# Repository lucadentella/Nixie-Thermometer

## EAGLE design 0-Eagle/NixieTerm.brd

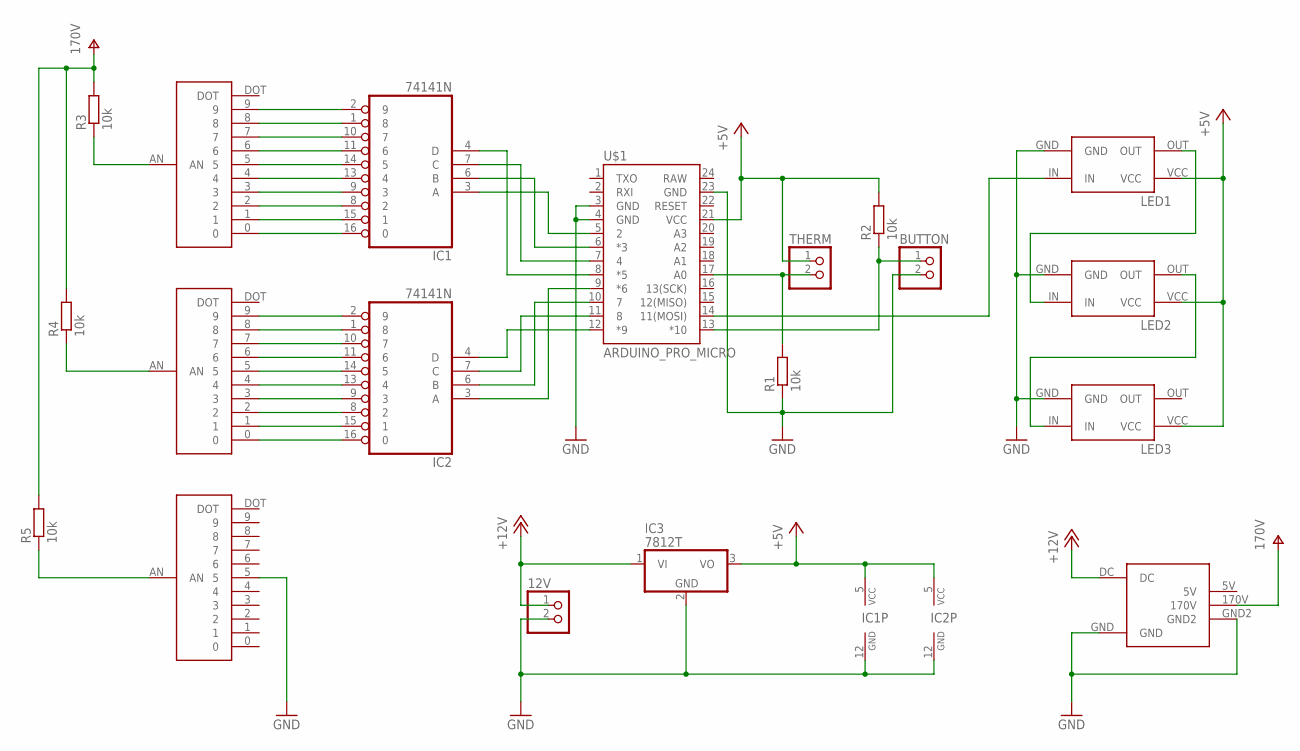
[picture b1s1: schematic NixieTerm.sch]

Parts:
12V: PINHD-1X2; 1X02
BUTTON: PINHD-1X2; 1X02
DEC: NIXIE-SOCKET; NIXIE-SOCKET-PAC
IC1, IC2: 74141N; DIL16
IC3: 7812T; TO220H
LED1, LED2, LED3: WS2812-LED; WS2812-LED-PAC
R1, R2, R3, R4, R5: 10k; 0207/12
SYM: NIXIE-SOCKET; NIXIE-SOCKET-PAC
THERM: PINHD-1X2; 1X02
U$1: ARDUINO_PRO_MICRO
U$2: NIXIE-SUPPLY; NIXIE-SUPPLY-PAC
UNIT: NIXIE-SOCKET; NIXIE-SOCKET-PAC

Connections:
+5V: IC1.5 (VCC), IC2.5 (VCC), IC3.3 (VO), LED1.VCC, LED2.VCC, LED3.VCC, R2.2, THERM.1, U$1.21 (VCC)
+12V: 12V.1, IC3.1 (VI), U$2.DC
GND: 12V.2, BUTTON.2, IC1.12 (GND), IC2.12 (GND), IC3.2 (GND), LED1.GND, LED2.GND, LED3.GND, R1.1, SYM.5, U$1.3 (GND), U$1.4 (GND), U$1.23 (GND), U$2.GND, U$2.GND2
unnamed: IC1.3 (A), U$1.5 (2)
unnamed: IC1.6 (B), U$1.6 (*3)
unnamed: IC1.7 (C), U$1.7 (4)
unnamed: IC1.4 (D), U$1.8 (*5)
unnamed: IC2.3 (A), U$1.9 (*6)
unnamed: IC2.6 (B), U$1.10 (7)
unnamed: IC2.7 (C), U$1.11 (8)
unnamed: IC2.4 (D), U$1.12 (*9)
unnamed: R1.2, THERM.2, U$1.17 (A0)
unnamed: BUTTON.1, R2.1, U$1.13 (*10)
unnamed: DEC.9, IC1.2 (9)
unnamed: LED1.OUT, LED2.IN
unnamed: LED2.OUT, LED3.IN
unnamed: LED1.IN, U$1.14 (11(MOSI))
unnamed: DEC.8, IC1.1 (8)
unnamed: DEC.7, IC1.10 (7)
unnamed: DEC.6, IC1.11 (6)
unnamed: DEC.5, IC1.14 (5)
unnamed: DEC.4, IC1.13 (4)
unnamed: DEC.3, IC1.9 (3)
unnamed: DEC.2, IC1.8 (2)
unnamed: DEC.1, IC1.15 (1)
unnamed: DEC.0, IC1.16 (0)
unnamed: IC2.2 (9), UNIT.9
unnamed: IC2.1 (8), UNIT.8
unnamed: IC2.10 (7), UNIT.7
unnamed: IC2.11 (6), UNIT.6
unnamed: IC2.14 (5), UNIT.5
unnamed: IC2.13 (4), UNIT.4
unnamed: IC2.9 (3), UNIT.3
unnamed: IC2.8 (2), UNIT.2
unnamed: IC2.15 (1), UNIT.1
unnamed: IC2.16 (0), UNIT.0
unnamed: DEC.AN, R3.1
unnamed: R4.1, UNIT.AN
unnamed: R5.1, SYM.AN
V+: R3.2, R4.2, R5.2, U$2.170V

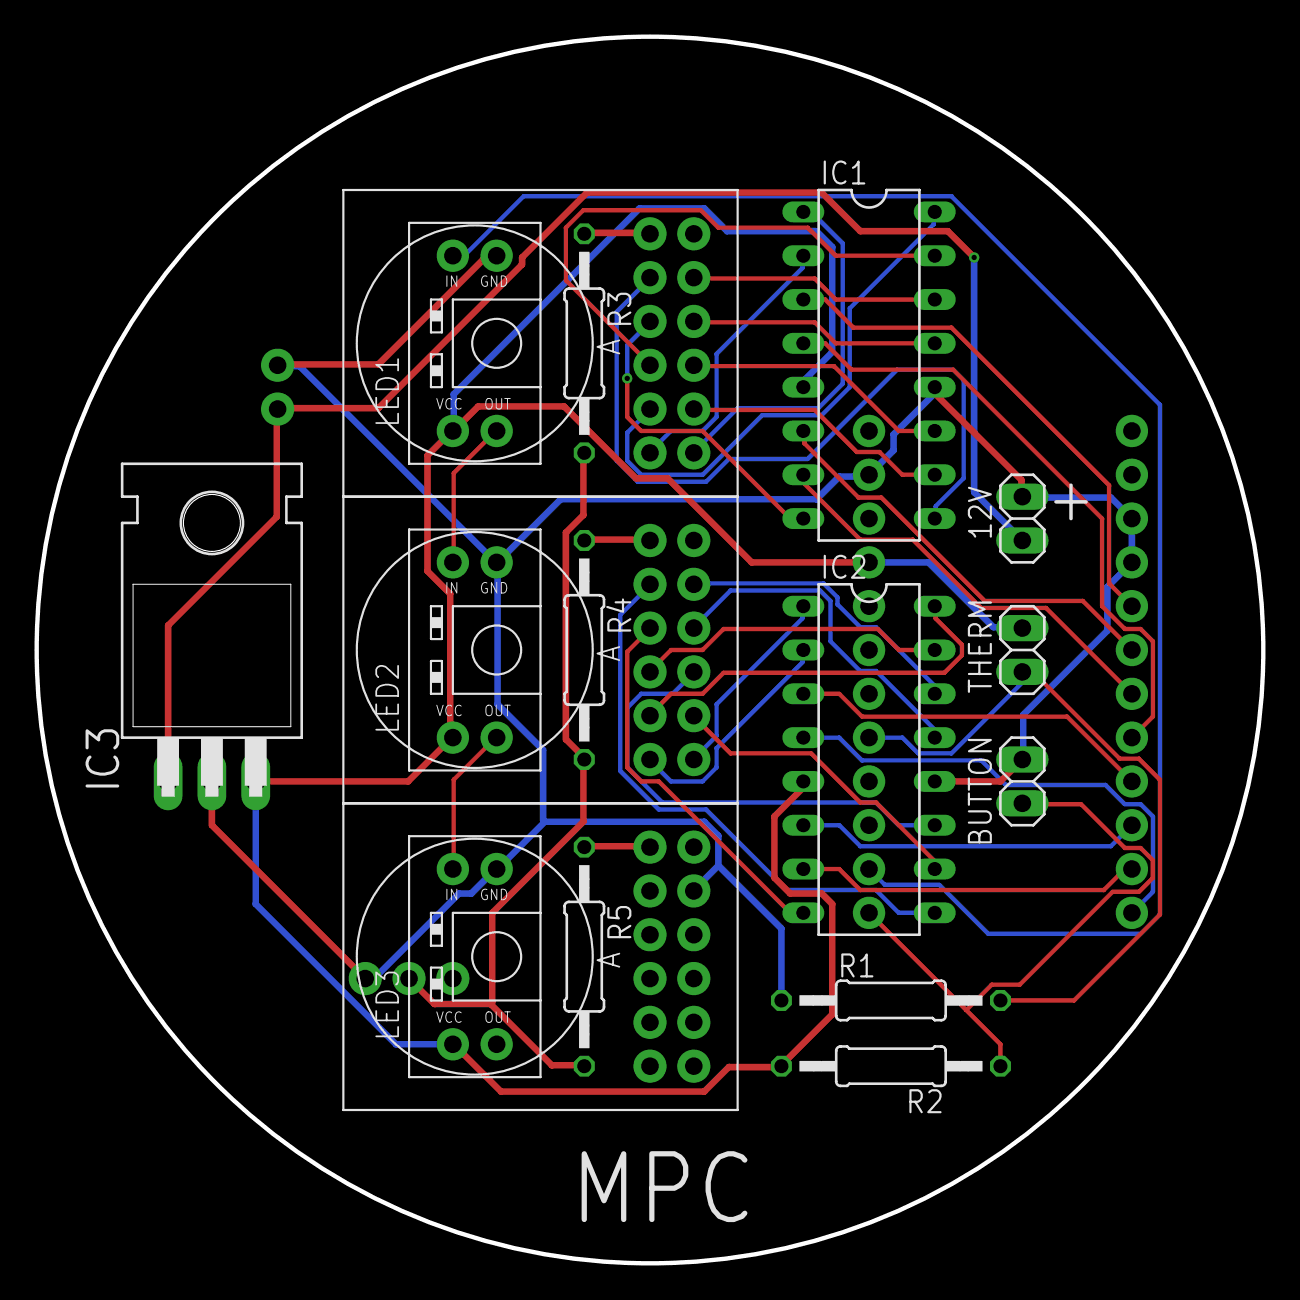
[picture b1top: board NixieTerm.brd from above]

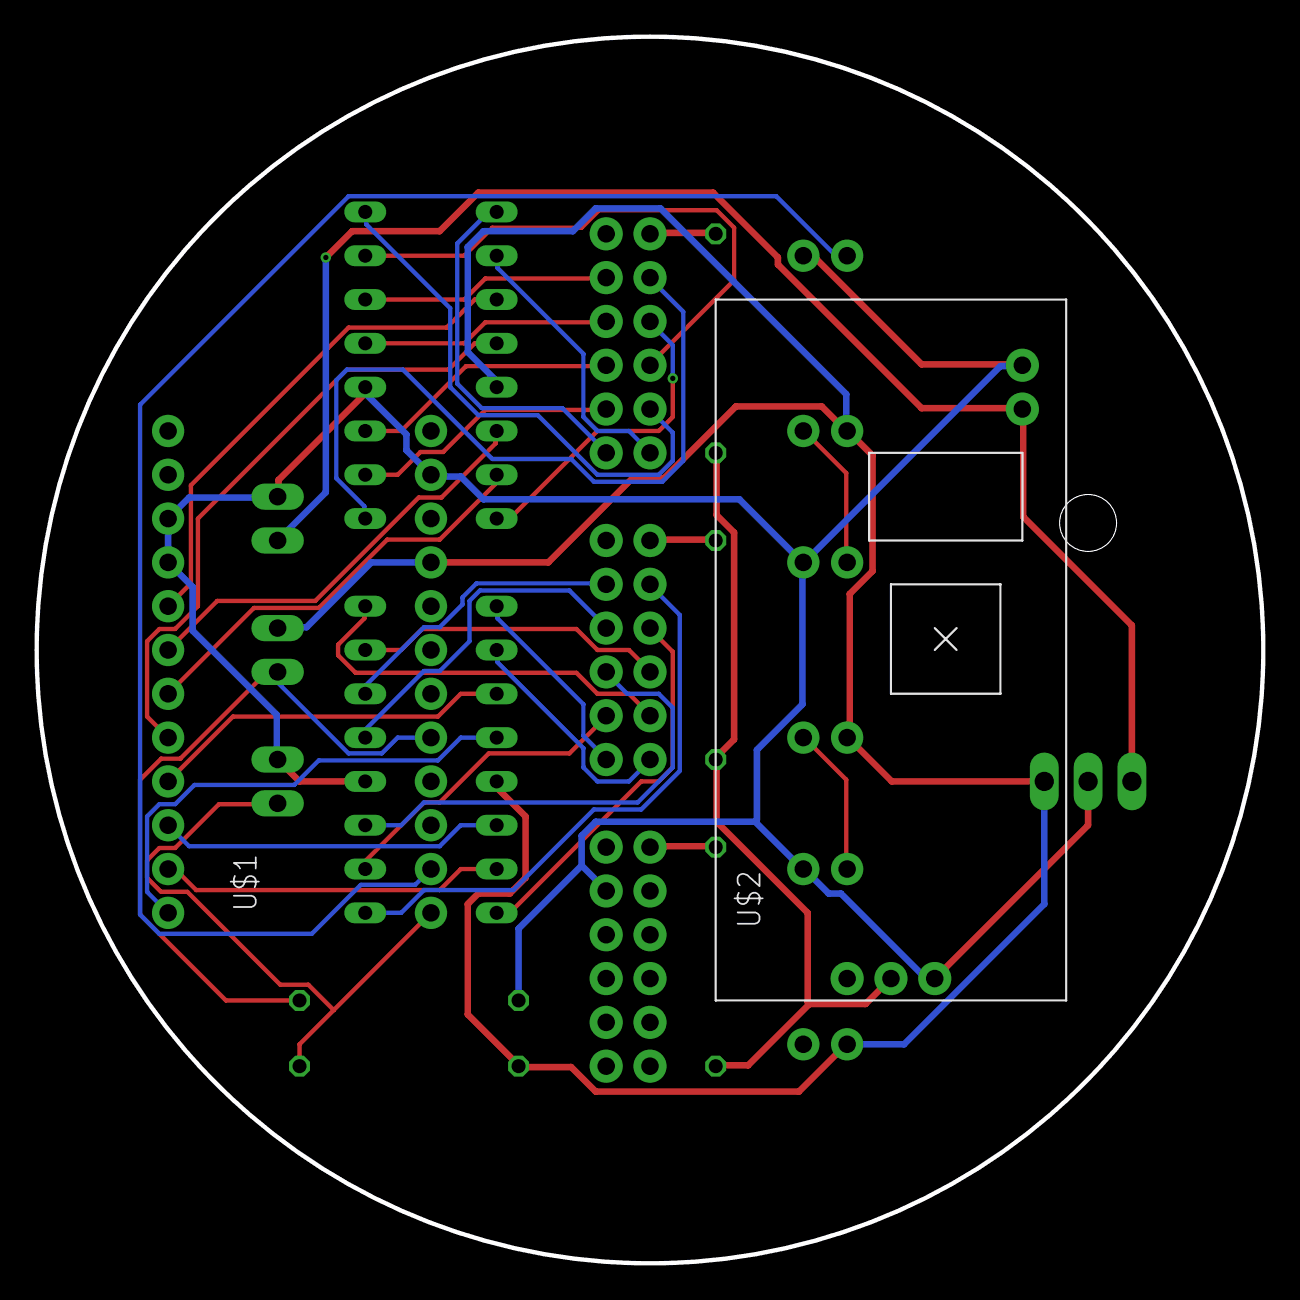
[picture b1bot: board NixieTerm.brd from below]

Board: 2 copper layers, 71.1 x 71.1 mm, 19 parts (2 on the bottom side), 40 nets.

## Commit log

2016-01-11 Counting example added
2016-01-12 DoubleCounting example added
2016-01-15 Thermistor example added
2016-01-18 Nixie temperature example added
2016-01-31 RGB Leds example added
2016-01-31 Final sketch added
2016-02-08 PCB files added

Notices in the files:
parts and their libraries:
SparkFun-Boards: Licensing: Creative Commons ShareAlike 4.0 International - https://creativecommons.org/licenses/by-sa/4.0
